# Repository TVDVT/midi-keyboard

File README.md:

# midi-keyboard

A piano-like keyboard that can play music.
I used to play the organ and the piano when I was young, so I want to make this a compact 2-in-1, where I can change the sound of each note! Sadly it only contains the white notes, but a lot can be made from these.

## Features 

- Three MX switches to play some beats
- Two rotary encoders (to adjust the pitch and volume)
- 7 capacitive touch keys (do, re, mi, fa, sol, la, si)
- 3 LED lights (DJ!)

## Schematic

## PCB 

## Case 
I made a case with a 10 degrees incline using Onshape. It now only has a bottom part, but I plan on making an upper one once I receive the 3d printer (fingers crossed!) </br>
https://cad.onshape.com/documents/c282bcd66a7a9d71e3e4bdfb/w/ad7d11d41164156ccb4d5c3b/e/60140dd8856affdbad1ca31e

## Firmware 
Right now it's a bit incomplete but it has the pins connected correctly, I borrowed it from the guide and will change it once I have everything.

## BOM

| Designator | Footprint | Quantity | Value | Supplier | Cost/item | Total Cost | LCSC Part # | Link |
|------------|-----------|----------|--------|----------|----------:|-----------:|-------------|------|
| D1, D2, D3 | LED_SK6812MINI-E_3.2x2.8mm_P1.5mm_ReverseMount | 3 | SK6812MINI-E | AliExpress | $1.12 | $3.36 | — | https://www.aliexpress.us/item/3256807677321116.html |
| J1 | touch | 1 | Capacitive Touch Buttons | — | — | — | — | — |
| SW1, SW4, SW6 | SW_Cherry_MX_1.00u_PCB | 3 | SW_Push | AliExpress | $0.23 | $0.69 | — | https://www.aliexpress.com/item/1005009946528694.html |
| SW2, SW3 | RotaryEncoder_Alps_EC11E-Switch_Vertical_H20mm | 2 | RotaryEncoder_Switch_MP | AliExpress | $0.72 | $1.44 | — | https://www.aliexpress.us/item/3256807457768762.html |
| U2 | Waveshare ESP32-S3-ZERO | 1 | Waveshare ESP32-S3-ZERO | AliExpress | $6.68 | $6.68 | — | https://www.aliexpress.com/item/1005007004089798.html |
| PCB | — | 1 | PCB | JLCPCB | $9.90 | $9.90 | — | https://jlcpcb.com/ |
| Case | — | 1 | 3D Printed Case | Printing Legion | $9.07 | $9.07 | — | — |
| Knobs | — | 2 | 3D Printed Rotary Encoder Knobs | Printing Legion | $0.07 | $0.14 | — | — |
| Shipping | — | 1 | Estimated Shipping | — | — | $7.00 | — | — |

### Cost Summary

| Item | Cost |
|------|-----:|
| Electronics & PCB Subtotal | $22.07 |
| 3D Printed Parts | $9.21 |
| Shipping | $7.00 |
| **Grand Total** | **$38.28** |

note: I have all the parts except for the PCB and Waveshare and 3d printed parts : $26.11

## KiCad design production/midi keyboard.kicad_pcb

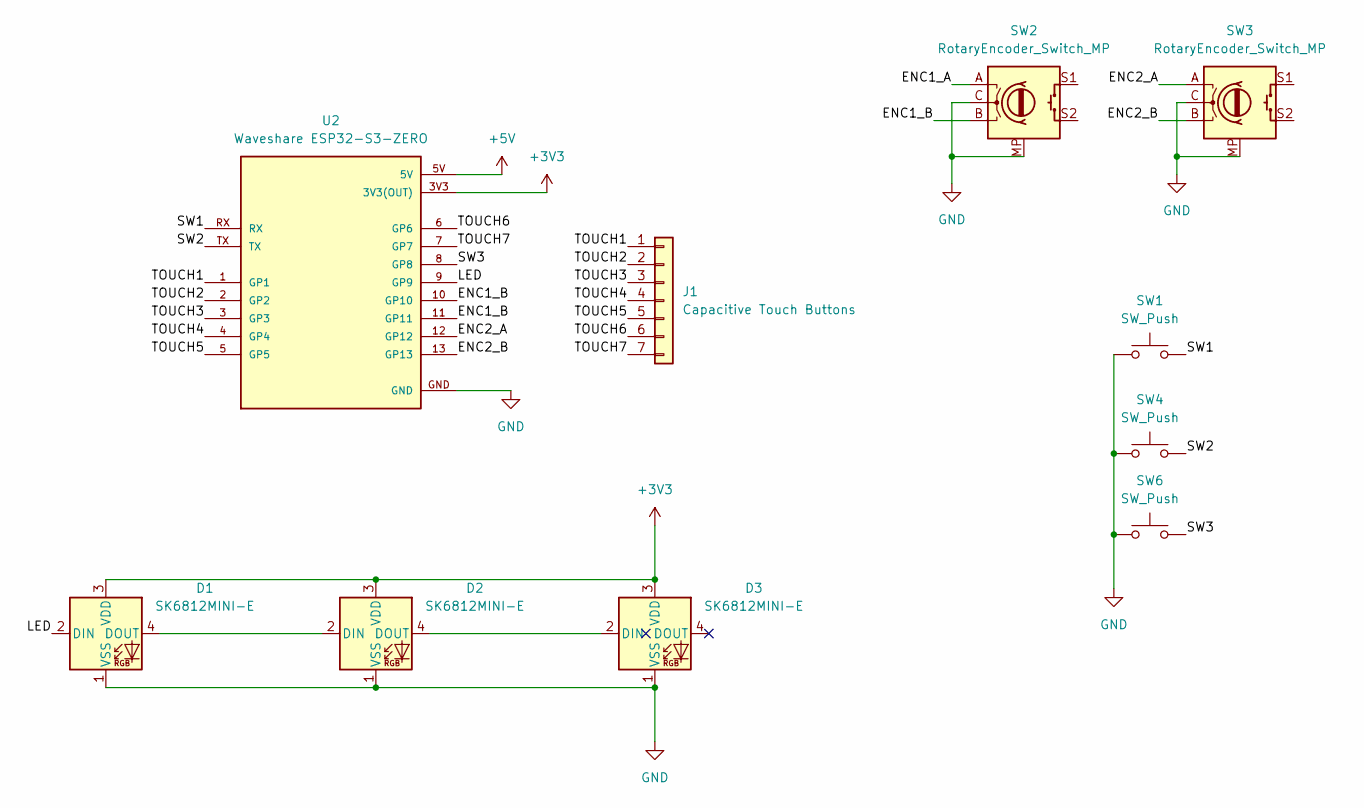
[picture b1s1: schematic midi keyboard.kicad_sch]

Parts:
D1, D2, D3: SK6812MINI-E; LED_SK6812MINI-E_3.2x2.8mm_P1.5mm_ReverseMount
J1: Capacitive Touch Buttons; touch
SW1, SW4, SW6: SW_Push; SW_Cherry_MX_1.00u_PCB
SW2, SW3: RotaryEncoder_Switch_MP; RotaryEncoder_Alps_EC11E-Switch_Vertical_H20mm
U2: Waveshare ESP32-S3-ZERO; Waveshare ESP32-S3-Zero; PARTREV NA

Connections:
+3V3: D1.3 (VDD), D2.3 (VDD), D3.3 (VDD), U2.3V3 (3V3(OUT))
+5V: U2.5V
/ENC1_A: SW2.A
/ENC1_B: SW2.B, U2.10 (GP10), U2.11 (GP11)
/ENC2_A: SW3.A, U2.12 (GP12)
/ENC2_B: SW3.B, U2.13 (GP13)
/LED: D1.2 (DIN), U2.9 (GP9)
/SW1: SW1.2, U2.RX
/SW2: SW4.2, U2.TX
/SW3: SW6.2, U2.8 (GP8)
/TOUCH1: J1.1, U2.1 (GP1)
/TOUCH2: J1.2, U2.2 (GP2)
/TOUCH3: J1.3, U2.3 (GP3)
/TOUCH4: J1.4, U2.4 (GP4)
/TOUCH5: J1.5, U2.5 (GP5)
/TOUCH6: J1.6, U2.6 (GP6)
/TOUCH7: J1.7, U2.7 (GP7)
GND: D1.1 (VSS), D2.1 (VSS), D3.1 (VSS), SW1.1, SW2.C, SW2.MP, SW3.C, SW3.MP, SW4.1, SW6.1, U2.GND
unnamed: D1.4 (DOUT), D2.2 (DIN)
unnamed: D2.4 (DOUT), D3.2 (DIN)

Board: 2 copper layers, 10 parts (3 on the bottom side), 18 nets, no tracks yet.

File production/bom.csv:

Designator,Footprint,Quantity,Value,LCSC Part #
"D1, D2, D3",LED_SK6812MINI-E_3.2x2.8mm_P1.5mm_ReverseMount,3,SK6812MINI-E,
J1,touch,1,Capacitive Touch Buttons,
"SW1, SW4, SW6",SW_Cherry_MX_1.00u_PCB,3,SW_Push,
"SW2, SW3",RotaryEncoder_Alps_EC11E-Switch_Vertical_H20mm,2,RotaryEncoder_Switch_MP,
U2,Waveshare ESP32-S3-Zero,1,Waveshare ESP32-S3-ZERO,
